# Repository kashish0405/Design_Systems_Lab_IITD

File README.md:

# Design & Systems Laboratory - IIT Delhi

## Mobile Phone Charger Design
- Designed of a SMPS based power supply for charging a mobile phone with following specifications -
  - The input of the charger is a standard , AC Mains supply.
  - It delivers a constant DC Output (up to 1A current).
  - The output voltage should settle to 5% of its final value in less than 5ms.
  - Stable output for a range of inputs (100V - 260V ).
- Prepared a comprehensive report Specifications, Simulation model and results, Enclosure Design and Bill of Materials.

## Robust Mule Bot Design
- Designed a 4-wheeled bot to follow customers with specific electrical, mechanical and functional requirements.
- Mule bots also have enhanced functionality of communication with each other.
- Prepared a comprehensive report with Specifications, Component Design and Model, Communication protocol and Bill of Materials.

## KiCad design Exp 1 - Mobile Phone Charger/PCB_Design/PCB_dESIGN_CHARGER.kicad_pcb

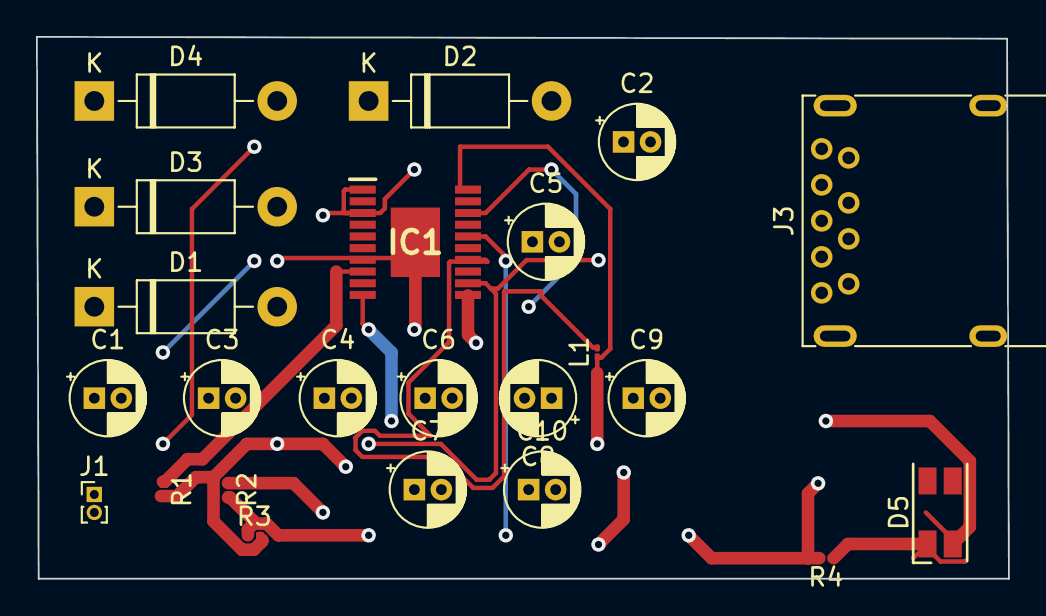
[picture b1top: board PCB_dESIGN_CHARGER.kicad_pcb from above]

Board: 6 copper layers, 54.0 x 30.1 mm, 23 parts (0 on the bottom side), 15 nets.

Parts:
C1, C2: 100u; CP_Radial_D4.0mm_P1.50mm
C3: 1000u; CP_Radial_D4.0mm_P1.50mm
C4: 1u; CP_Radial_D4.0mm_P1.50mm
C5, C10: 2.2u; CP_Radial_D4.0mm_P1.50mm
C6: 0.005u; CP_Radial_D4.0mm_P1.50mm
C7: 4.7p; CP_Radial_D4.0mm_P1.50mm
C8: 0.1u; CP_Radial_D4.0mm_P1.50mm
C9: 47u; CP_Radial_D4.0mm_P1.50mm
D1, D2, D3, D4: 1N4007; D_DO-41_SOD81_P10.16mm_Horizontal
D5: LED; LED_RGB_1210
IC1: LT8631EFE#PBF; SOP65P640X120-21N
J1: Conn_01x02; PinHeader_1x02_P1.00mm_Vertical
J3: USB_A; USB3_A_Molex_48393-001
L1: 22u; L_01005_0402Metric
R1: 25.5k; R_0201_0603Metric
R2: 1Meg; R_0201_0603Metric
R3: 191k; R_0201_0603Metric
R4: 1k; R_0201_0603Metric

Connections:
GND: C3.2, C4.2, C5.2, C6.2, C9.2, C10.2, D1.2, D2.2, IC1.7, IC1.21, J3.4, J3.5, R1.2, R3.2, R4.2
unnamed: C1.1, J1.2
unnamed: C1.2, C2.1, D1.1, D3.2
unnamed: C2.2, D2.1, D4.2, J1.1
unnamed: C3.1, C4.1, C5.1, D3.1, D4.1, IC1.1, IC1.3
unnamed: C6.1, IC1.10
unnamed: C7.1, C9.1, D5.2, IC1.12, J3.1, R2.1
unnamed: C7.2, IC1.11, R2.2, R3.1
unnamed: C8.1, IC1.20, L1.1
unnamed: C8.2, IC1.18
unnamed: C10.1, IC1.16
unnamed: D5.1, R4.1
unnamed: IC1.8, R1.1
unnamed: IC1.14, L1.2
unnamed: J3.2, J3.3
